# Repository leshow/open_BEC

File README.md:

# micro_bec

A small step-down BEC, copied  matek micro BEC 6-30V as best I could

- Input: 6-30V (2-6S)
- Output: 5V by default, 9V with JP1 bridged (9V needs 3S or more)
- Current: 1.5A continuous, 2.5A peak
- Size: about 14 x 10mm, one 4-pin 2.54mm header

## Circuit

TI LMR51430YFDDCR synchronous buck (4.5-36V in, 3A, 1.1MHz, forced PWM), TSOT-23-6.

| Part          | Value                                           |
| ------------- | ----------------------------------------------- |
| Input caps    | 2x 4.7uF 50V                                    |
| Bootstrap cap | 100nF, CB to SW                                 |
| Inductor      | 4.7uH, Isat 4.5A                                |
| Output caps   | 2x 22uF 25V 0805                                |
| Feedback      | 100k top, 13.7k bottom, 15k + JP1 to GND for 9V |

Output voltage is `0.6V x (1 + 100k / R)`:

- JP1 open: R = 13.7k, ~4.98V
- JP1 bridged: R = 13.7k || 15k, ~8.98V

## Pinout

| Pin            | Net  |
| -------------- | ---- |
| 1 (square pad) | VIN  |
| 2              | GND  |
| 3              | GND  |
| 4              | VOUT |

## Libraries

The inductor footprint is in `libs.pretty`, pulled from LCSC with `easyeda2kicad`.
Add it as a footprint library named `mp2315` with path `${KIPRJMOD}/libs.pretty`
(Preferences > Manage Footprint Libraries > Project Specific Libraries).

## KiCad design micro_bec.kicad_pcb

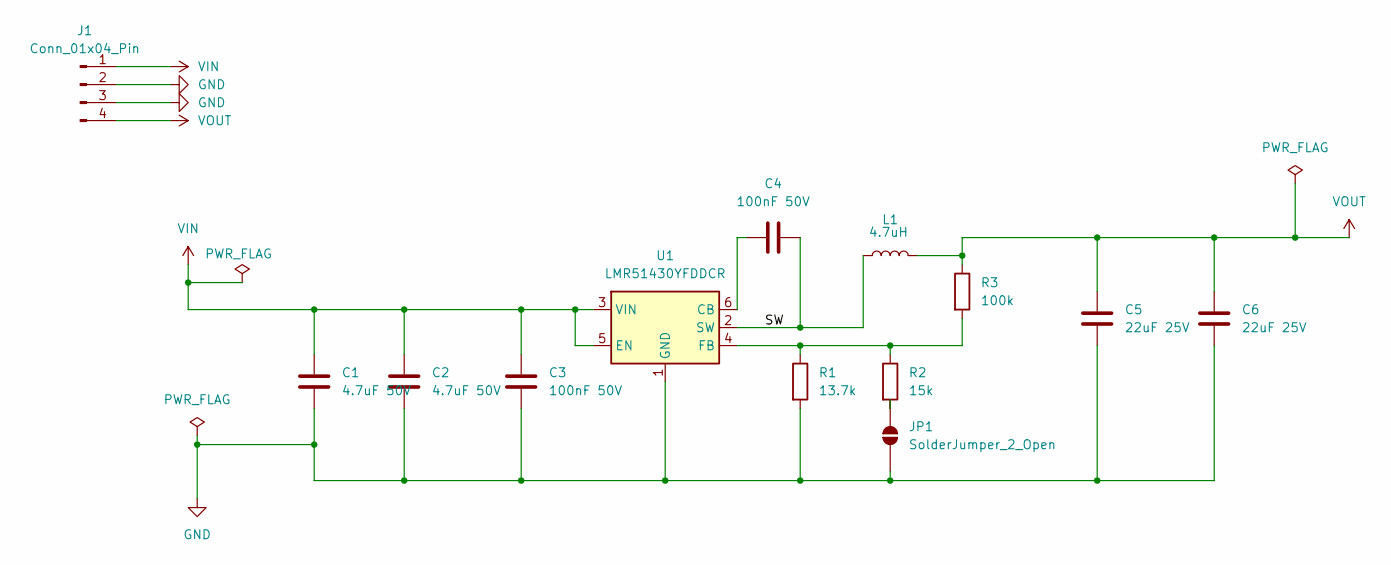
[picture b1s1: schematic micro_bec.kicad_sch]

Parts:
C1, C2: 4.7uF 50V; C_1206_3216Metric; LCSC C51205
C3, C4: 100nF 50V; C_0402_1005Metric; LCSC C307331
C5, C6: 22uF 25V; C_0805_2012Metric; LCSC C45783
J1: Conn_01x04_Pin; PinHeader_1x04_P2.54mm_Vertical
JP1: SolderJumper_2_Open; SolderJumper-2_P1.3mm_Open_Pad1.0x1.5mm
L1: 4.7uH; L_Changjiang_FTC303018D; LCSC C5832388
R1: 13.7k; R_0402_1005Metric; LCSC C25854
R2: 15k; R_0402_1005Metric; LCSC C25756
R3: 100k; R_0402_1005Metric; LCSC C25741
U1: LMR51430YFDDCR; TSOT-23-6; LCSC C5219261

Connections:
/SW: C4.1, L1.1, U1.2 (SW)
GND: C1.2, C2.2, C3.2, C5.2, C6.2, J1.2, J1.3, JP1.2 (B), R1.2, U1.1 (GND)
unnamed: JP1.1 (A), R2.2
unnamed: C4.2, U1.6 (CB)
unnamed: R1.1, R2.1, R3.2, U1.4 (FB)
VIN: C1.1, C2.1, C3.1, J1.1, U1.3 (VIN), U1.5 (EN)
VOUT: C5.1, C6.1, J1.4, L1.2, R3.1

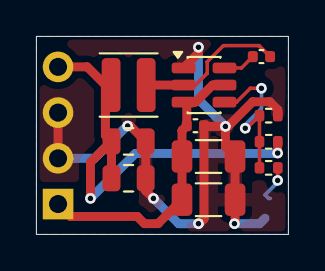
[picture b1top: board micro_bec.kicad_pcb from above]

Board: 2 copper layers, 14.0 x 11.0 mm, 13 parts (1 on the bottom side), 7 nets.

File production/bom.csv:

Designator,Footprint,Quantity,Value,LCSC Part #
"C1, C2",1206,2,4.7uF 50V,C51205
"C3, C4",0402,2,100nF 50V,C307331
"C5, C6",0805,2,22uF 25V,C45783
L1,L_Changjiang_FTC303018D,1,4.7uH,C5832388
R1,0402,1,13.7k,C25854
R2,0402,1,15k,C25756
R3,0402,1,100k,C25741
U1,TSOT-23-6,1,LMR51430YFDDCR,C5219261
